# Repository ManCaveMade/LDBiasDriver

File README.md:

## LDBiasDriver
Copyright Mitchell A. Cox (mitch@enox.co.za)

If you use this design, please acknowledge me in any resulting publications.

### What is it?

1. A low noise laser diode bias driver which uses the ThorLabs MLD203P1 constant power and also the MLD203CLN constanct current (better for fast modulation systems which use a Bias-Tee) bias driver. https://www.thorlabs.com/thorproduct.cfm?partnumber=MLD203P1 and https://www.thorlabs.com/thorproduct.cfm?partnumber=MLD203CLN

2. An Arduino based controller for the CC version is WIP. This controller will allow greater than 12 bits of control of the output current as well as digital monitoring of the actual current, etc. I also plan on creating a user friendly MATLAB GUI for it.

#### Features

* Input voltage: 6 - 18 V
* Output current: < 200 mA @ 3.0 V
* Laser current monitor output: 0.1V/mA wrt. GND (can be changed by changing resistors on op-amp)
* Over current protection resistor (R3)
* Sexy red power on LED
* Compact
* SMA for DC bias output (easy connection direct to Bias-Tee)
* ~3 uA noise
 
Designed with Eagle 7.7

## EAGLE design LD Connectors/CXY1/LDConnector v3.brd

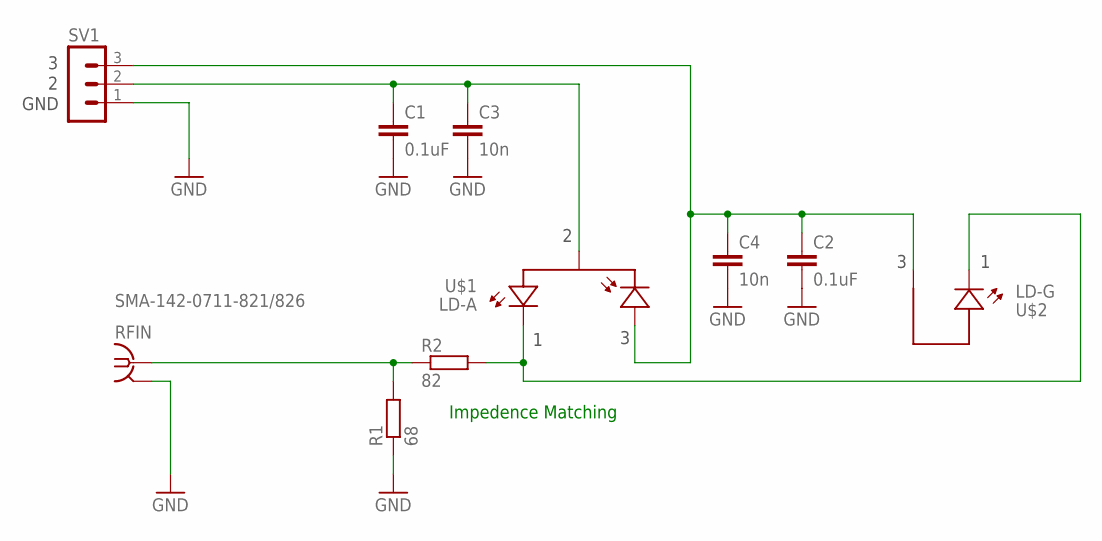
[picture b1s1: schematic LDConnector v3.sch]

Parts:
C1, C2: 0.1uF; C0603
C3, C4: 10n; C0603
R1: 68; R0603
R2: 82; R0603
RFIN: SMA-142-0711-821/826; J502-ND-142-0711-821/826
SV1: MA03-1
U$1: LD-A; TYPEA
U$2: LD-G; TYPEG

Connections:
GND: C1.2, C2.2, C3.2, C4.2, R1.1, RFIN.G@1 (2), RFIN.G@2 (2), RFIN.G@3 (2), RFIN.G@4 (2), SV1.1
unnamed: C1.1, C3.1, SV1.2, U$1.2-PDC-LDA (LDA-PDC)
unnamed: R2.2, U$1.1-LDC (LDC), U$2.1-LDC (LDC)
unnamed: R1.2, R2.1, RFIN.1
unnamed: C2.1, C4.1, SV1.3, U$1.3-PDA (PDA), U$2.3-LDA (LDA)

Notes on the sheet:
Impedence Matching
GND

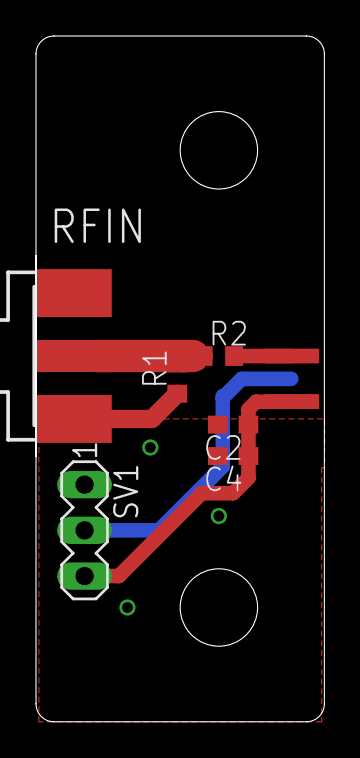
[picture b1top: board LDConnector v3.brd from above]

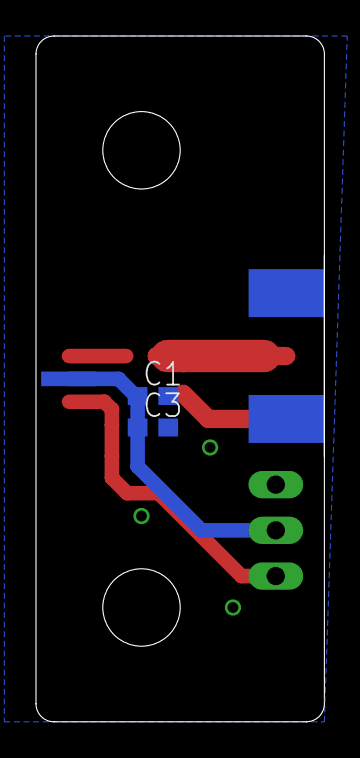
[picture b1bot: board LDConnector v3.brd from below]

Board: 2 copper layers, 16.0 x 38.1 mm, 10 parts (2 on the bottom side), 5 nets.

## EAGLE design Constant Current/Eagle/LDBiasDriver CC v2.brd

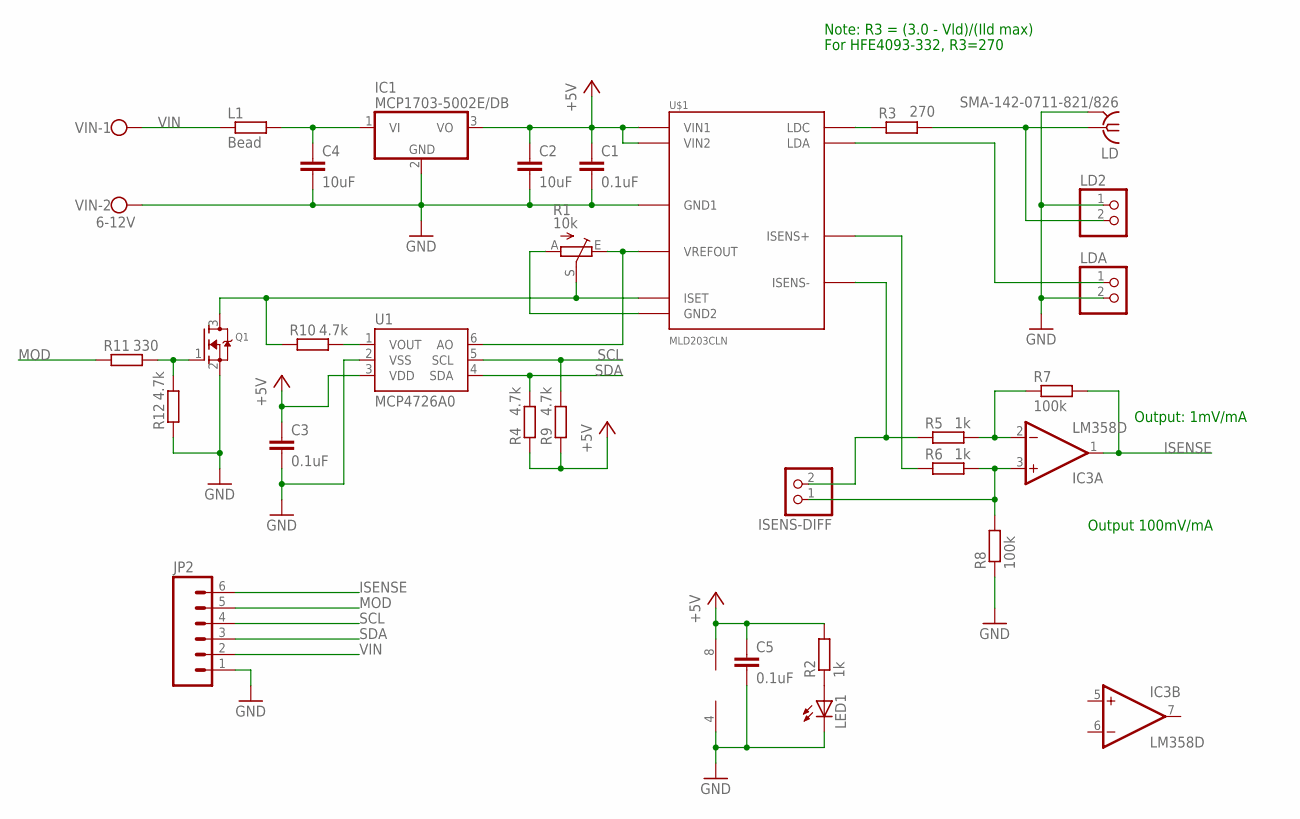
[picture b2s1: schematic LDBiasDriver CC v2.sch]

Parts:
C1, C3, C5: 0.1uF; C0805
C2, C4: 10uF; C0805
IC1: MCP1703-5002E/DB; SOT223
IC3: LM358D; SO08
ISENS-DIFF: PINHD-1X2; 1X02
JP2: M06POLAR_LOCK; MOLEX-1X6_LOCK
L1: Bead; R0805
LD: SMA-142-0711-821/826; J502-ND-142-0711-821/826
LD2: PINHD-1X2; 1X02
LDA: PINHD-1X2; 1X02
LED1: LEDCHIPLED_1206; CHIPLED_1206
Q1: MOSFET-NREFLOW; SOT23
R1: 10k; RJ9W
R2, R5, R6: 1k; R0805
R3: 270; R0805
R4, R9, R10, R12: 4.7k; R0805
R7, R8: 100k; R0805
R11: 330; R0805
U1: MCP4726A0; SOT23-6
U$1: MLD203CLN; MLD203
VIN: 6-12V; W237-102

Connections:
+5V: C1.1, C2.1, C3.1, C5.1, IC1.3 (VO), IC3.8 (V+), R2.2, R4.1, R9.1, U1.3 (VDD), U$1.P$1 (VIN1), U$1.P$2 (VIN2)
GND: C1.2, C2.2, C3.2, C4.2, C5.2, IC1.2 (GND), IC3.4 (V-), JP2.1, LD.G@1 (2), LD.G@2 (2), LD.G@3 (2), LD.G@4 (2), LD2.1, LDA.2, LED1.C, Q1.2 (S), R8.1, R12.1, U1.2 (VSS), U$1.P$3 (GND1), VIN.2
ISENSE: IC3.1 (OUT), JP2.6, R7.2
MOD: JP2.5, R11.1
unnamed: R1.E, U1.6 (AO), U$1.P$5 (VREFOUT)
unnamed: LED1.A, R2.1
unnamed: Q1.3 (D), R1.S, R10.1, U$1.P$6 (ISET)
unnamed: R1.A, U$1.P$4 (GND2)
unnamed: R6.1, U$1.P$12 (ISENS+)
unnamed: ISENS-DIFF.2, R5.1, U$1.P$13 (ISENS-)
unnamed: LD.1, LD2.2, R3.2
unnamed: R3.1, U$1.P$11 (LDC)
unnamed: Q1.1 (G), R11.2, R12.2
unnamed: LDA.1, U$1.P$14 (LDA)
unnamed: R10.2, U1.1 (VOUT)
unnamed: C4.1, IC1.1 (VI), L1.2
unnamed: IC3.2 (-IN), R5.2, R7.1
unnamed: IC3.3 (+IN), ISENS-DIFF.1, R6.2, R8.2
SCL: JP2.4, R9.2, U1.5 (SCL)
SDA: JP2.3, R4.2, U1.4 (SDA)
VIN: JP2.2, L1.1, VIN.1

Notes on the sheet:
Note: R3 = (3.0 - Vld)/(Ild max)
For HFE4093-332, R3=270
Output: 1mV/mA
Output 100mV/mA

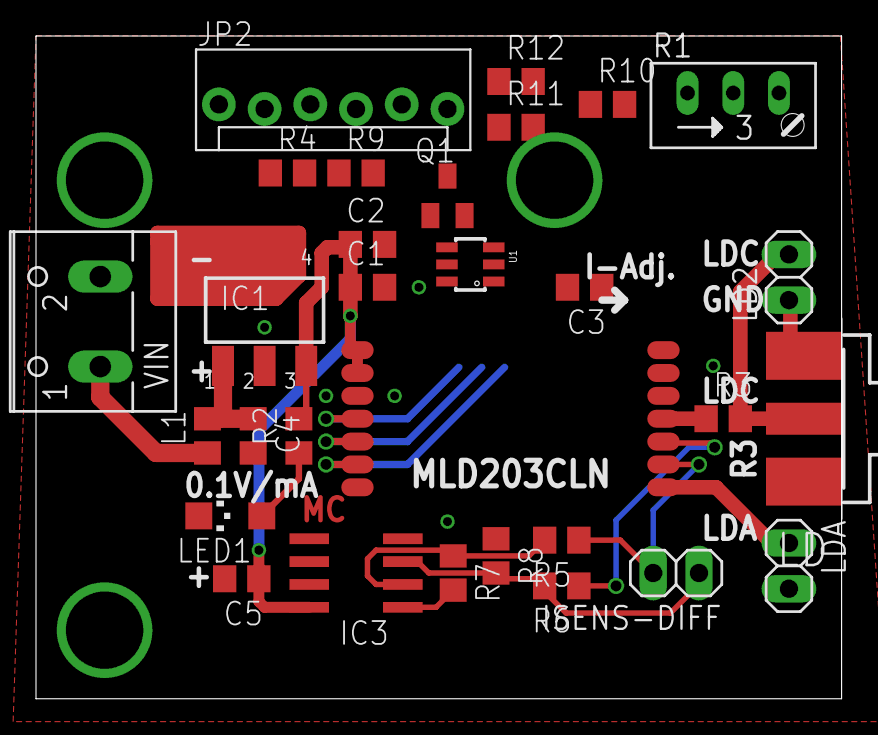
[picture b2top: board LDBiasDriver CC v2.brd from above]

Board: 2 copper layers, 44.8 x 36.8 mm, 30 parts (0 on the bottom side), 21 nets.

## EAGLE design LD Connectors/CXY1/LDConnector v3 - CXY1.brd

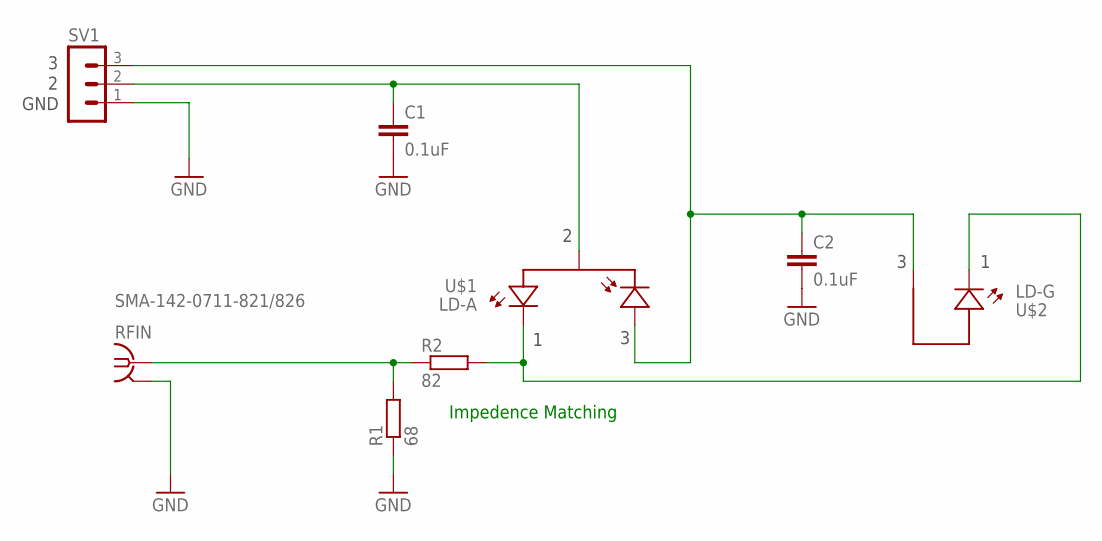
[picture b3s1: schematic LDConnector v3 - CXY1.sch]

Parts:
C1, C2: 0.1uF; C0603
R1: 68; R0603
R2: 82; R0603
RFIN: SMA-142-0711-821/826; J502-ND-142-0711-821/826
SV1: MA03-1
U$1: LD-A; TYPEA
U$2: LD-G; TYPEG

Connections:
GND: C1.2, C2.2, R1.1, RFIN.G@1 (2), RFIN.G@2 (2), RFIN.G@3 (2), RFIN.G@4 (2), SV1.1
unnamed: C1.1, SV1.2, U$1.2-PDC-LDA (LDA-PDC)
unnamed: R2.2, U$1.1-LDC (LDC), U$2.1-LDC (LDC)
unnamed: R1.2, R2.1, RFIN.1
unnamed: C2.1, SV1.3, U$1.3-PDA (PDA), U$2.3-LDA (LDA)

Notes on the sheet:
Impedence Matching
GND

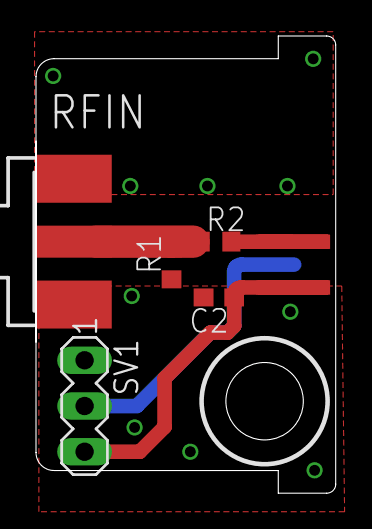
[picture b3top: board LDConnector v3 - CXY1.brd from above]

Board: 2 copper layers, 16.6 x 25.4 mm, 8 parts (1 on the bottom side), 5 nets.

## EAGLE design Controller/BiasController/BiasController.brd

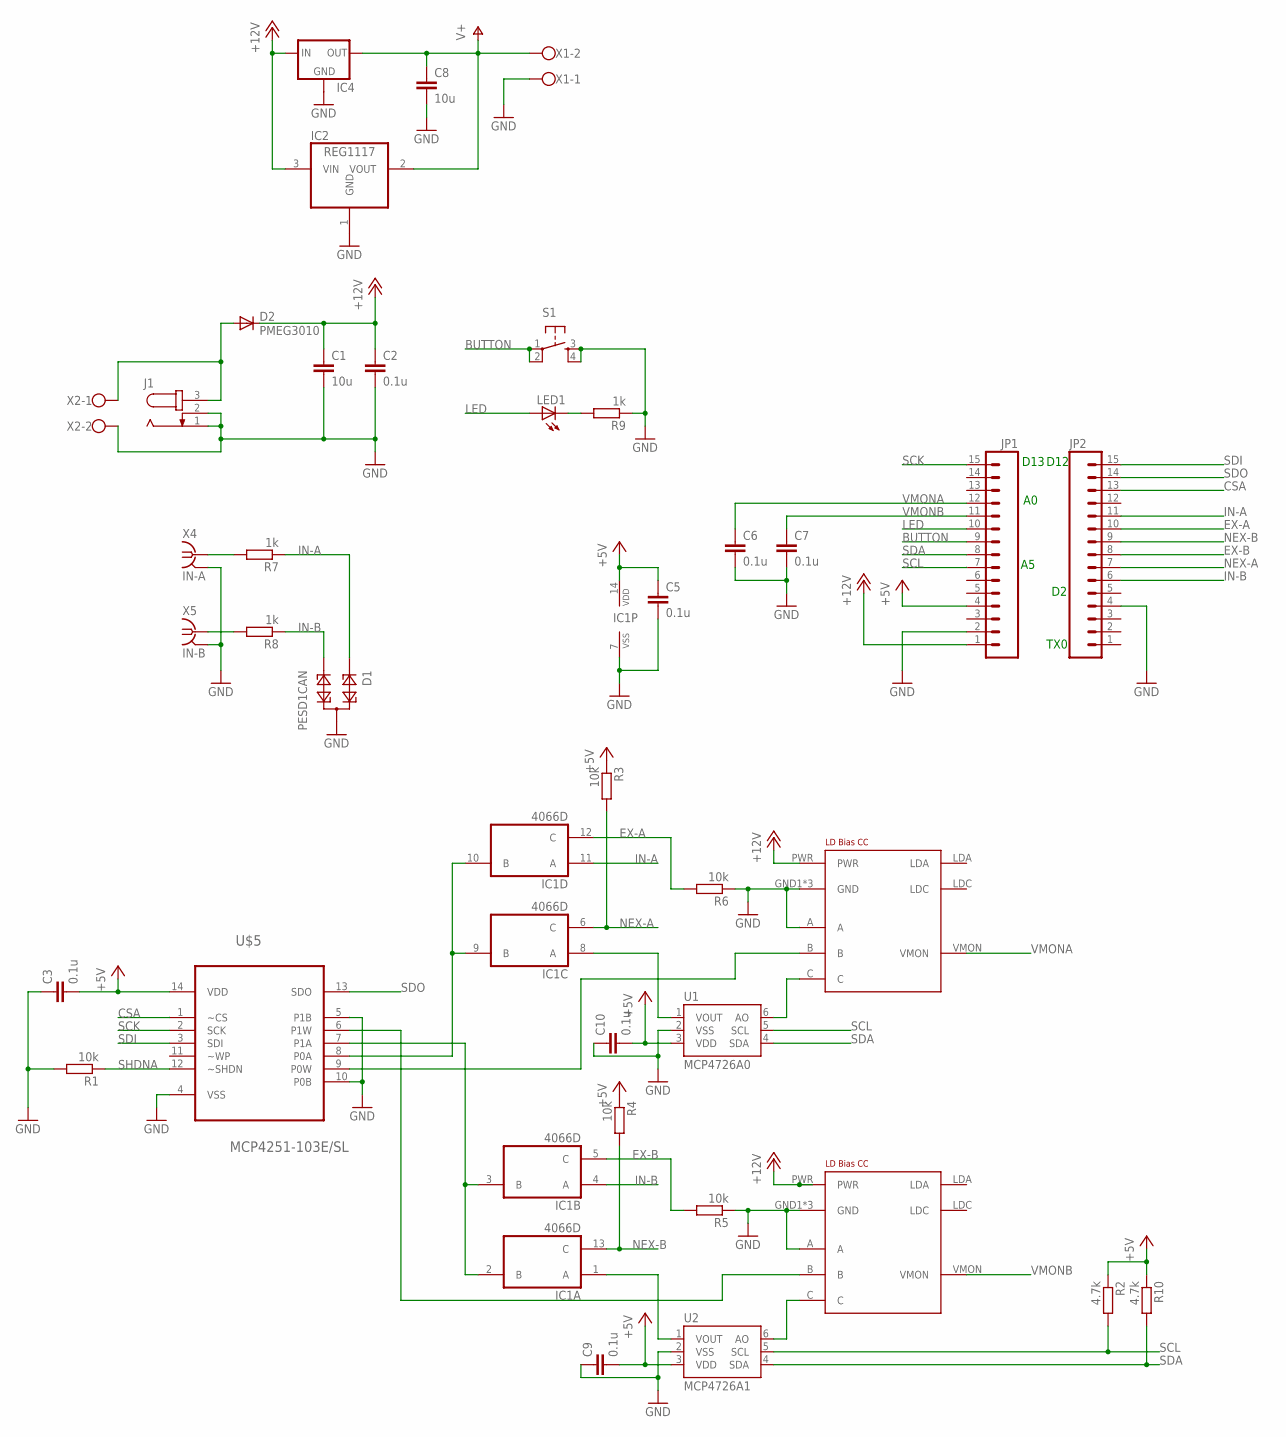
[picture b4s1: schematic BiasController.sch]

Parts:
C1, C8: 10u; C0805
C2, C3, C5, C6, C7, C9, C10: 0.1u; C0805
D1: PESD1CAN; SOT23
D2: PMEG3010; SOD-323
IC1: 4066D; SO14
IC2: REG1117; SOT223
IC4: 78XXS
J1: JACK-PLUG0; SPC4077
JP1, JP2: M15LOCK_LONGPADS; 1X15_LOCK_LONGPADS
LED1: LED0603; LED-0603
R1, R3, R4, R5, R6: 10k; R0805
R2, R10: 4.7k; R0805
R7, R8, R9: 1k; R0805
S1: TAC_SWITCHPTH; TACTILE-PTH
U1: MCP4726A0; SOT23-6
U2: MCP4726A1; SOT23-6
U$1, U$2: LDBIASCC; LDBIASDRIVERCC
U$5: MCP4251-103E/SL; SOIC127P600X175-14N
X1, X2: W237-102
X4: IN-A; J502-ND-142-0711-821/826
X5: IN-B; J502-ND-142-0711-821/826

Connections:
+5V: C3.2, C5.1, C9.2, C10.2, IC1.14 (VDD), JP1.4, R2.1, R3.1, R4.1, R10.1, U1.3 (VDD), U2.3 (VDD), U$5.14 (VDD)
+12V: C1.1, C2.1, D2.1 (C), IC2.3 (VIN), IC4.IN, JP1.1, U$1.PWR, U$2.PWR
BUTTON: JP1.9, S1.1, S1.2
CSA: JP2.13, U$5.1 (~CS)
EX-A: IC1.12 (C), JP2.10, R6.2
EX-B: IC1.5 (C), JP2.8, R5.2
GND: C1.2, C2.2, C3.1, C5.2, C6.2, C7.2, C8.2, C9.1, C10.1, D1.3, IC1.7 (VSS), IC2.1 (GND), IC4.GND, J1.1, J1.2, JP1.2, JP2.4, R1.2, R5.1, R6.1, R9.1, S1.3, S1.4, U1.2 (VSS), U2.2 (VSS), U$1.A, U$1.GND1 (GND), U$1.GND2 (GND), U$1.GND3 (GND), U$2.A, U$2.GND1 (GND), U$2.GND2 (GND), U$2.GND3 (GND), U$5.4 (VSS), U$5.5 (P1B), U$5.10 (P0B), X1.1, X2.2, X4.G@1 (2), X4.G@2 (2), X4.G@3 (2), X4.G@4 (2), X5.G@1 (2), X5.G@2 (2), X5.G@3 (2), X5.G@4 (2)
IN-A: D1.1, IC1.11 (A), JP2.11, R7.1
IN-B: D1.2, IC1.4 (A), JP2.6, R8.1
LED: JP1.10, LED1.A
unnamed: U1.6 (AO), U$1.C
unnamed: IC1.8 (A), U1.1 (VOUT)
unnamed: U$1.B, U$5.9 (P0W)
unnamed: IC1.9 (B), IC1.10 (B), U$5.8 (P0A)
unnamed: IC1.2 (B), IC1.3 (B), U$5.7 (P1A)
unnamed: U2.6 (AO), U$2.C
unnamed: D2.2 (A), J1.3, X2.1
unnamed: LED1.C, R9.2
unnamed: R7.2, X4.1
unnamed: R8.2, X5.1
unnamed: IC1.1 (A), U2.1 (VOUT)
unnamed: U$2.B, U$5.6 (P1W)
NEX-A: IC1.6 (C), JP2.7, R3.2
NEX-B: IC1.13 (C), JP2.9, R4.2
SCK: JP1.15, U$5.2 (SCK)
SCL: JP1.7, R2.2, U1.5 (SCL), U2.5 (SCL)
SDA: JP1.8, R10.2, U1.4 (SDA), U2.4 (SDA)
SDI: JP2.15, U$5.3 (SDI)
SDO: JP2.14, U$5.13 (SDO)
SHDNA: R1.1, U$5.12 (~SHDN)
V+: C8.1, IC2.2 (VOUT), IC4.OUT, X1.2
VMONA: C6.1, JP1.12, U$1.VMON
VMONB: C7.1, JP1.11, U$2.VMON

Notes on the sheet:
D13
D12
TX0

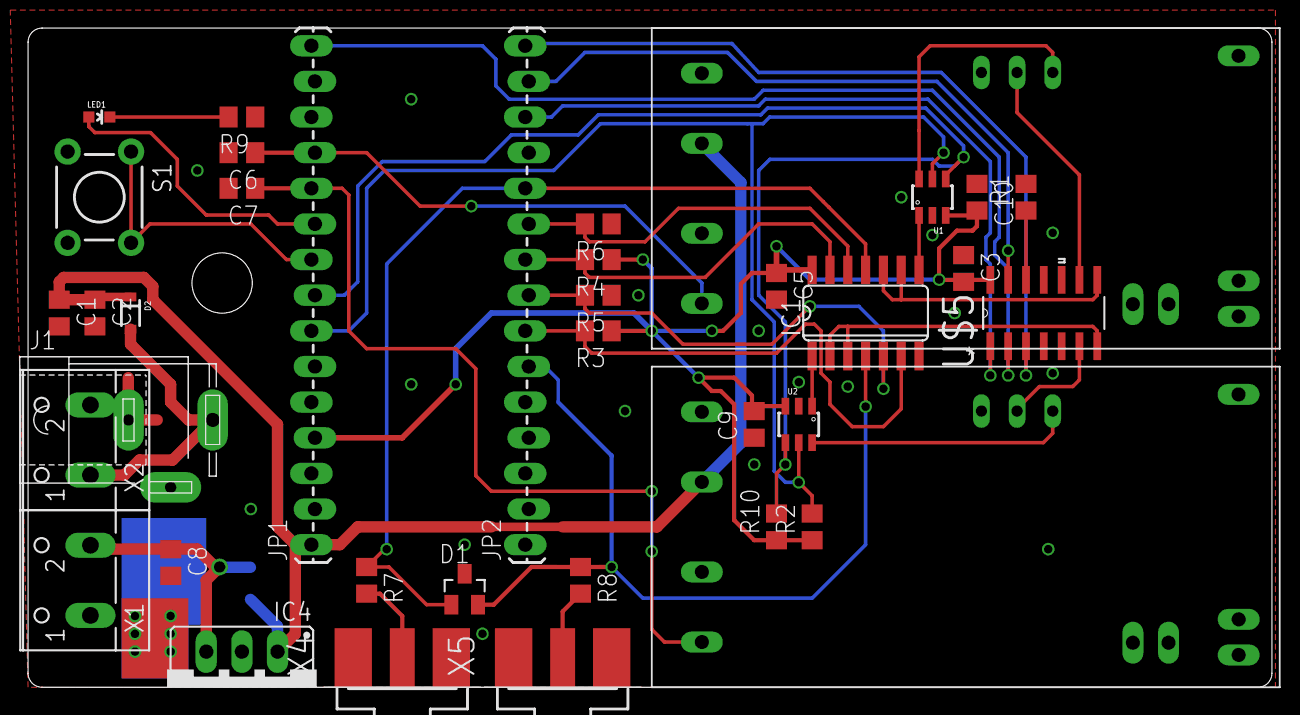
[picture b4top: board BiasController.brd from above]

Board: 2 copper layers, 88.7 x 47.0 mm, 38 parts (1 on the bottom side), 33 nets.

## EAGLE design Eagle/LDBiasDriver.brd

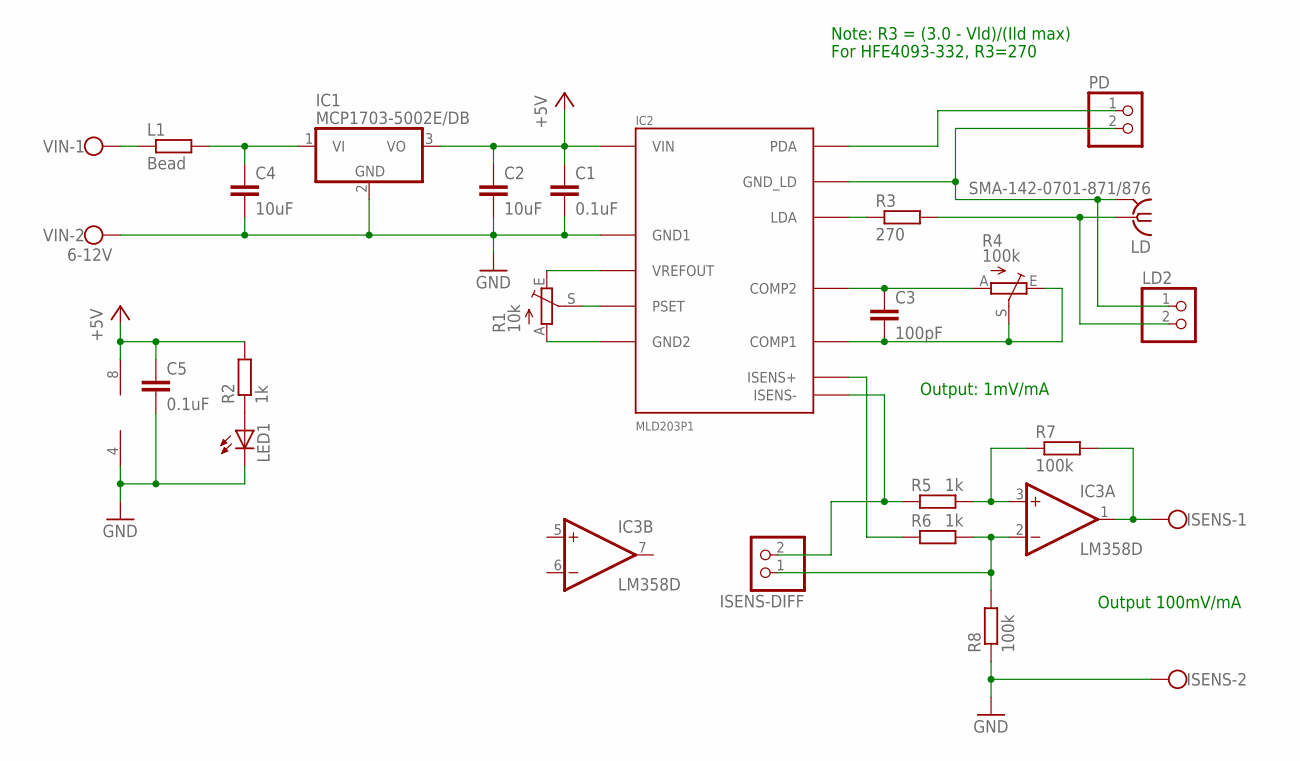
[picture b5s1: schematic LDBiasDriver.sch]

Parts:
C1, C5: 0.1uF; C0805
C2, C4: 10uF; C0805
C3: 100pF; C0805
IC1: MCP1703-5002E/DB; SOT223
IC2: MLD203P1; MLD203
IC3: LM358D; SO08
ISENS: W237-102
ISENS-DIFF: PINHD-1X2; 1X02
L1: Bead; R0805
LD: SMA-142-0701-871/876; J502-ND-142-0701-871/876
LD2: PINHD-1X2; 1X02
LED1: LEDCHIPLED_1206; CHIPLED_1206
PD: PINHD-1X2; 1X02
R1: 10k; RJ9W
R2, R5, R6: 1k; R0805
R3: 270; R0805
R4: 100k; RJ9W
R7, R8: 100k; R0805
VIN: 6-12V; W237-102

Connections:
+5V: C1.1, C2.1, C5.1, IC1.3 (VO), IC2.P$1 (VIN), IC2.P$2 (VIN), IC3.8 (V+), R2.2
GND: C1.2, C2.2, C4.2, C5.2, IC1.2 (GND), IC2.P$3 (GND1), IC3.4 (V-), ISENS.2, LED1.C, R8.1, VIN.2
unnamed: IC2.P$6 (PSET), R1.S
unnamed: LED1.A, R2.1
unnamed: IC2.P$5 (VREFOUT), R1.E
unnamed: IC2.P$4 (GND2), R1.A
unnamed: IC2.P$12 (ISENS+), R6.1
unnamed: IC2.P$13 (ISENS-), ISENS-DIFF.2, R5.1
unnamed: LD.1, LD2.2, R3.2
unnamed: IC2.P$14 (LDA), R3.1
unnamed: IC2.P$11 (GND_LD), LD.G@1 (2), LD.G@2 (2), LD.G@3 (2), LD.G@4 (2), LD2.1, PD.2
unnamed: IC2.P$8 (PDA), PD.1
unnamed: C3.2, IC2.P$10 (COMP1), R4.E, R4.S
unnamed: C3.1, IC2.P$9 (COMP2), R4.A
unnamed: L1.1, VIN.1
unnamed: C4.1, IC1.1 (VI), L1.2
unnamed: IC3.3 (+IN), R5.2, R7.1
unnamed: IC3.2 (-IN), ISENS-DIFF.1, R6.2, R8.2
unnamed: IC3.1 (OUT), ISENS.1, R7.2

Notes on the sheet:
Note: R3 = (3.0 - Vld)/(Ild max)
For HFE4093-332, R3=270
Output: 1mV/mA
Output 100mV/mA

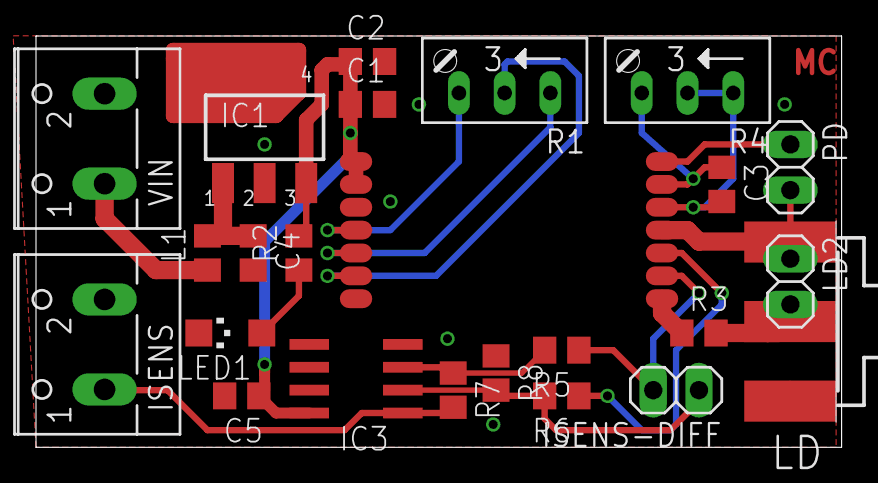
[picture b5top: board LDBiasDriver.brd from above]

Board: 2 copper layers, 44.8 x 22.9 mm, 24 parts (0 on the bottom side), 19 nets.

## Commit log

2016-11-06 Add license
2016-11-06 initial commit for v1.0
2016-11-06 v1.1 WIP with enhancements: > documentation on the PCB > removed stop on some vias for easier adjustement > added holes in case SMA connector not used
2016-11-06 used a standard connector spacing for the SMA alternative.
2016-11-06 readme
2016-11-22 Updates based on experience
2016-11-29 Changed directory structure to have separate CC and CP versions
2016-11-29 Added a CC version
2017-02-05 added controller
2017-02-06 controller done but going to change
2017-02-18 final version as manufactured
2017-02-20 clean up and pdf generation
2017-02-22 added LDConnector board to fit into a ThorLabs CXY1 (or other SM1) holder.

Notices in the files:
parts and their libraries:
SparkFun-AnalogIC: Licensing:Creative Commons ShareAlike 4.0 International - https://creativecommons.org/licenses/by-sa/4.0
SparkFun: Licensing: CC v3.0 Share-Alike You are welcome to use this library for commercial purposes.
